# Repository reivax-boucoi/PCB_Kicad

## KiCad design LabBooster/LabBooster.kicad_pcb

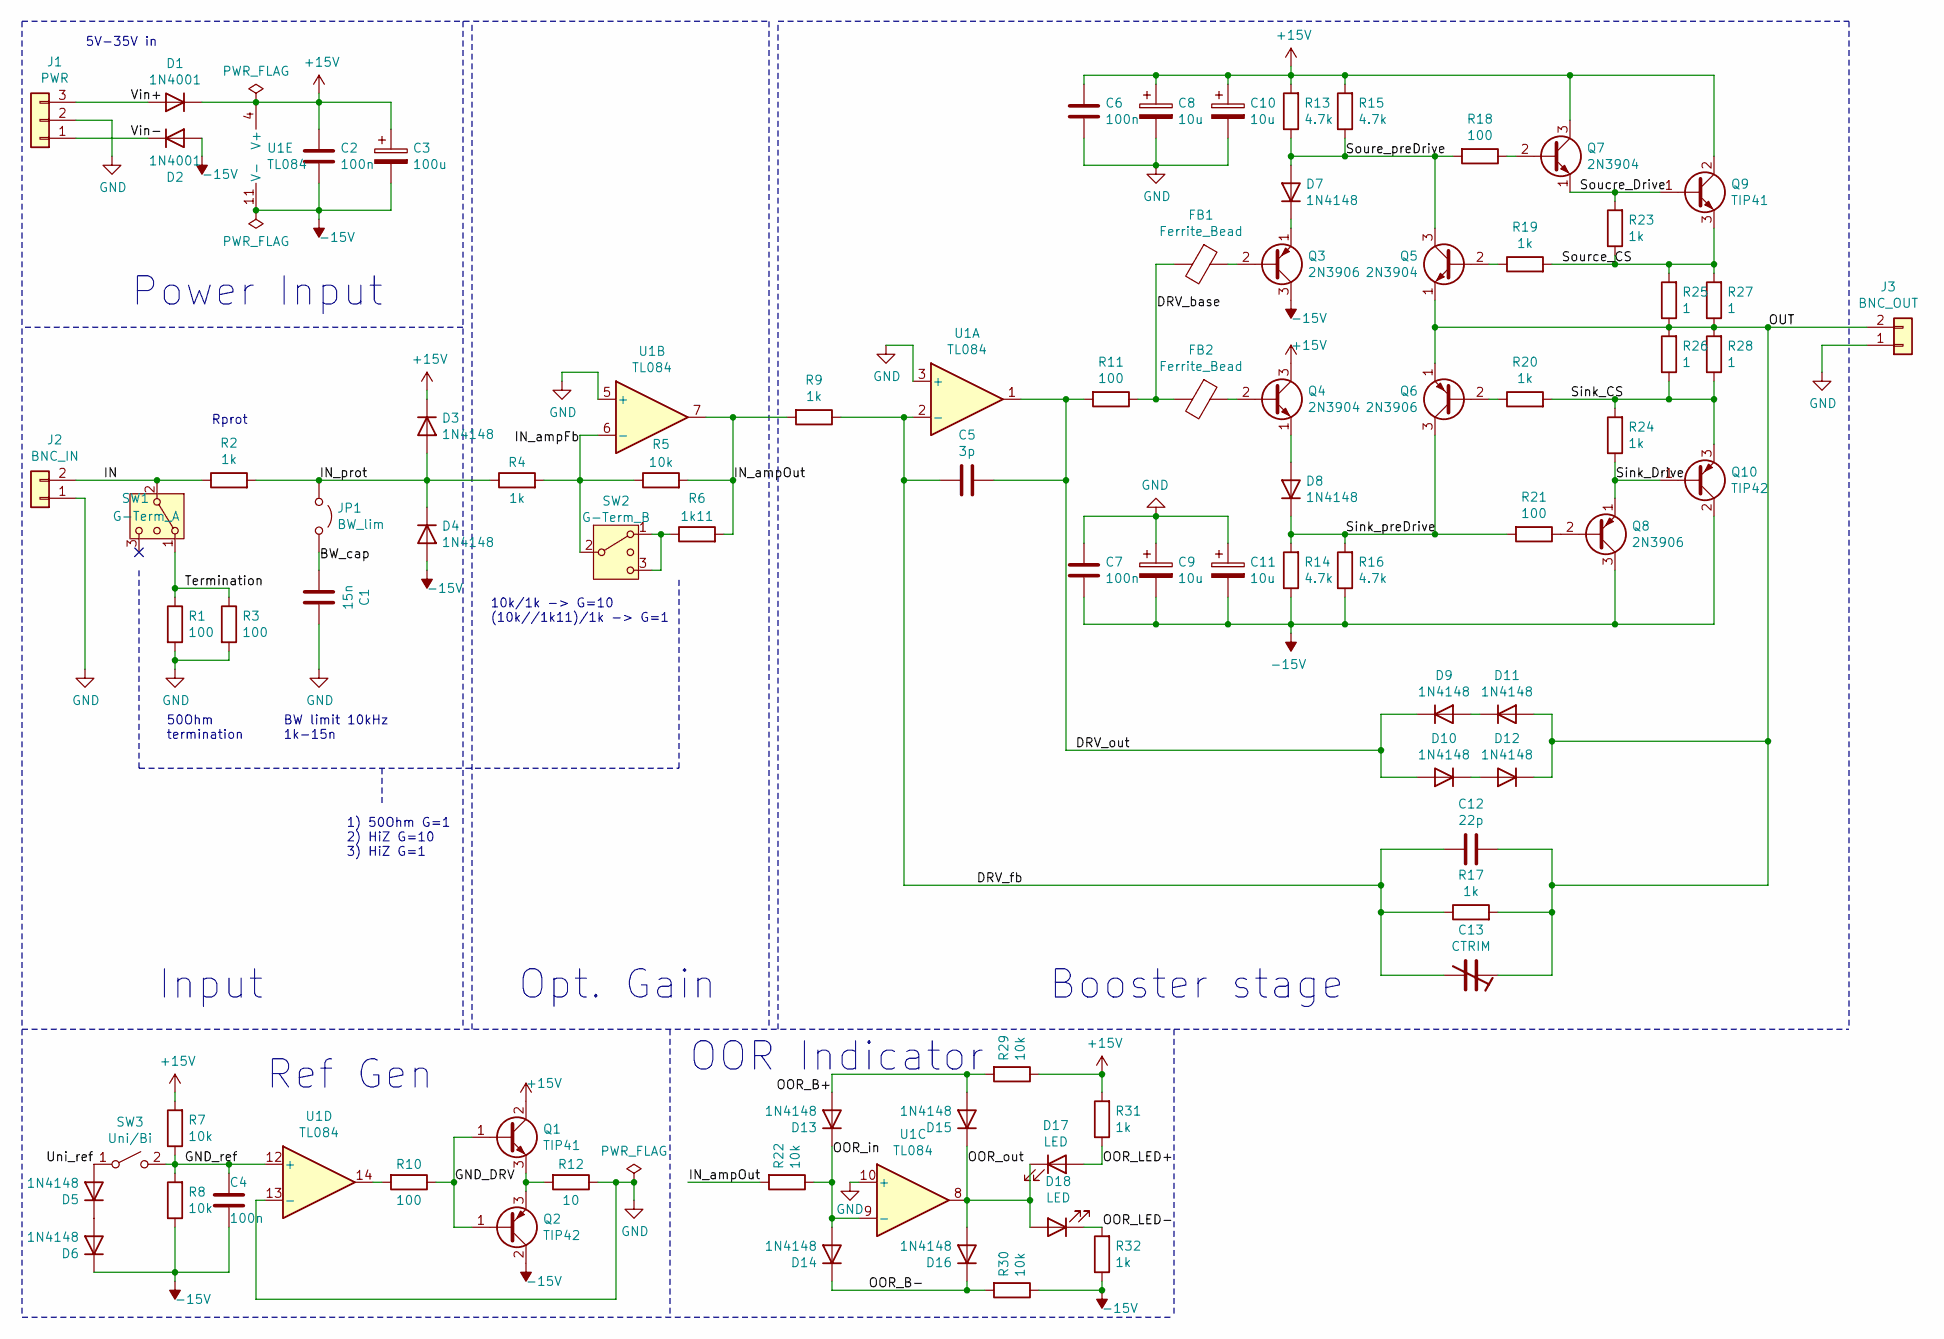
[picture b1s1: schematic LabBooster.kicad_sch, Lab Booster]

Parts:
C1: 15n; C_Socket_D5.0mm_W2.5mm_P5.00mm
C2, C4, C6, C7: 100n; C_Disc_D5.0mm_W2.5mm_P5.00mm
C3: 100u; CP_Radial_D10.0mm_P5.00mm
C5: 3p; C_Socket_D5.0mm_W2.5mm_P5.00mm
C8, C9, C10, C11: 10u; CP_Radial_D6.3mm_P2.50mm
C12: 22p; C_Socket_D5.0mm_W2.5mm_P5.00mm
C13: CTRIM
D1, D2: 1N4001; D_DO-41_SOD81_P10.16mm_Horizontal
D3, D4, D5, D6, D7, D8, D9, D10, D11, D12, D13, D14, D15, D16: 1N4148; D_DO-35_SOD27_P7.62mm_Horizontal
D17, D18: LED; LED_D3.0mm
FB1, FB2: Ferrite_Bead; R_Axial_DIN0309_L9.0mm_D3.2mm_P12.70mm_Horizontal
J1: PWR; SolderWirePad_1x03_P4.445mm_Drill1.5mm
J2: BNC_IN; SolderWirePad_1x02_P5.08mm_Drill1.5mm
J3: BNC_OUT; SolderWirePad_1x02_P5.08mm_Drill1.5mm
JP1: BW_lim; PinSocket_1x02_P2.54mm_Vertical
Q1, Q9: TIP41; TO-220-3_Vertical
Q2, Q10: TIP42; TO-220-3_Vertical
Q3, Q6, Q8: 2N3906; TO-92_Inline
Q4, Q5, Q7: 2N3904; TO-92_Inline
R1, R3, R10, R11, R18, R21: 100; R_Axial_DIN0207_L6.3mm_D2.5mm_P10.16mm_Horizontal
R2: 1k; R_Socket_L6.3mm_D2.5mm_P10.16mm_Horizontal
R4, R9, R17, R19, R20, R23, R24, R31, R32: 1k; R_Axial_DIN0207_L6.3mm_D2.5mm_P10.16mm_Horizontal
R5, R7, R8, R29, R30: 10k; R_Axial_DIN0207_L6.3mm_D2.5mm_P10.16mm_Horizontal
R6: 1k11; R_Socket_L6.3mm_D2.5mm_P10.16mm_Horizontal
R12: 10; R_Socket_L6.3mm_D2.5mm_P10.16mm_Horizontal
R13, R14, R15, R16: 4.7k; R_Axial_DIN0207_L6.3mm_D2.5mm_P10.16mm_Horizontal
R22: 10k; R_Socket_L6.3mm_D2.5mm_P10.16mm_Horizontal
R25, R26, R27, R28: 1; R_Axial_DIN0207_L6.3mm_D2.5mm_P10.16mm_Horizontal
SW1: G-Term_A; PinHeader_1x03_P2.54mm_Vertical
SW2: G-Term_B; PinHeader_1x03_P2.54mm_Vertical
SW3: Uni/Bi; PinSocket_1x02_P2.54mm_Vertical
U1: TL084; DIP-14_W7.62mm

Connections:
+15V: C2.1, C3.1, C6.1, C8.1, C10.1, D1.1 (K), D3.1 (K), Q1.2 (C), Q4.3 (C), Q7.3 (C), Q9.2 (C), R7.2, R13.2, R15.2, R29.1, R31.2, U1.4 (V+)
-15V: C2.2, C3.2, C4.2, C7.2, C9.2, C11.2, D2.2 (A), D4.2 (A), D6.1 (K), Q2.2 (C), Q3.3 (C), Q8.3 (C), Q10.2 (C), R8.1, R14.1, R16.1, R30.1, R32.1, U1.11 (V-)
/BW_cap: C1.2, JP1.2 (B)
/DRV_base: FB1.2, FB2.2, R11.1
/DRV_fb: C5.2, C12.2, C13.2, R9.1, R17.1, U1.2 (-)
/DRV_out: C5.1, D9.1 (K), D10.2 (A), R11.2, U1.1
/GND_DRV: Q1.1 (B), Q2.1 (B), R10.1
/GND_ref: C4.1, R7.1, R8.2, SW3.2 (B), U1.12 (+)
/IN: J2.2, R2.1, SW1.2 (3)
/IN_ampFb: R4.2, R5.1, SW2.2 (3), U1.6 (-)
/IN_ampOut: R5.2, R6.2, R9.2, R22.2, U1.7
/IN_prot: D3.2 (A), D4.1 (K), JP1.1 (A), R2.2, R4.1
/OOR_B+: D13.2 (A), D15.2 (A), R29.2
/OOR_B-: D14.1 (K), D16.1 (K), R30.2
/OOR_LED+: D17.2 (A), R31.1
/OOR_LED-: D18.1 (K), R32.2
/OOR_in: D13.1 (K), D14.2 (A), R22.1, U1.9 (-)
/OOR_out: D15.1 (K), D16.2 (A), D17.1 (K), D18.2 (A), U1.8
/OUT: C12.1, C13.1, D11.2 (A), D12.1 (K), J3.2, Q5.1 (E), Q6.1 (E), R17.2, R25.1, R26.2, R27.1, R28.2
/Sink_CS: Q10.3 (E), R20.2, R24.2, R26.1, R28.1
/Sink_Drive: Q8.1 (E), Q10.1 (B), R24.1
/Sink_preDrive: D8.1 (K), Q6.3 (C), R14.2, R16.2, R21.2
/Soucre_Drive: Q7.1 (E), Q9.1 (B), R23.2
/Source_CS: Q9.3 (E), R19.2, R23.1, R25.2, R27.2
/Soure_preDrive: D7.2 (A), Q5.3 (C), R13.1, R15.1, R18.2
/Termination: R1.1, R3.1, SW1.1
/Uni_ref: D5.2 (A), SW3.1 (A)
/Vin+: D1.2 (A), J1.3
/Vin-: D2.1 (K), J1.1
GND: C1.1, C6.2, C7.1, C8.2, C9.1, C10.2, C11.1, J1.2, J2.1, J3.1, R1.2, R3.2, R12.1, U1.3 (+), U1.5 (+), U1.10 (+), U1.13 (-)
unnamed: D5.1 (K), D6.2 (A)
unnamed: D7.1 (K), Q3.1 (E)
unnamed: D8.2 (A), Q4.1 (E)
unnamed: D10.1 (K), D12.2 (A)
unnamed: D9.2 (A), D11.1 (K)
unnamed: FB1.1, Q3.2 (B)
unnamed: FB2.1, Q4.2 (B)
unnamed: Q1.3 (E), Q2.3 (E), R12.2
unnamed: Q5.2 (B), R19.1
unnamed: Q6.2 (B), R20.1
unnamed: Q7.2 (B), R18.1
unnamed: Q8.2 (B), R21.1
unnamed: R6.1, SW2.1, SW2.3 (4)
unnamed: R10.2, U1.14

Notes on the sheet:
5V-35V in
Opt. Gain
Power Input
50Ohm termination
Input
10k/1k -> G=10 (10k//1k11)/1k -> G=1
Ref Gen
BW limit 10kHz 1k-15n
1) 50Ohm G=1 2) HiZ G=10 3) HiZ G=1
Booster stage
Rprot
OOR Indicator

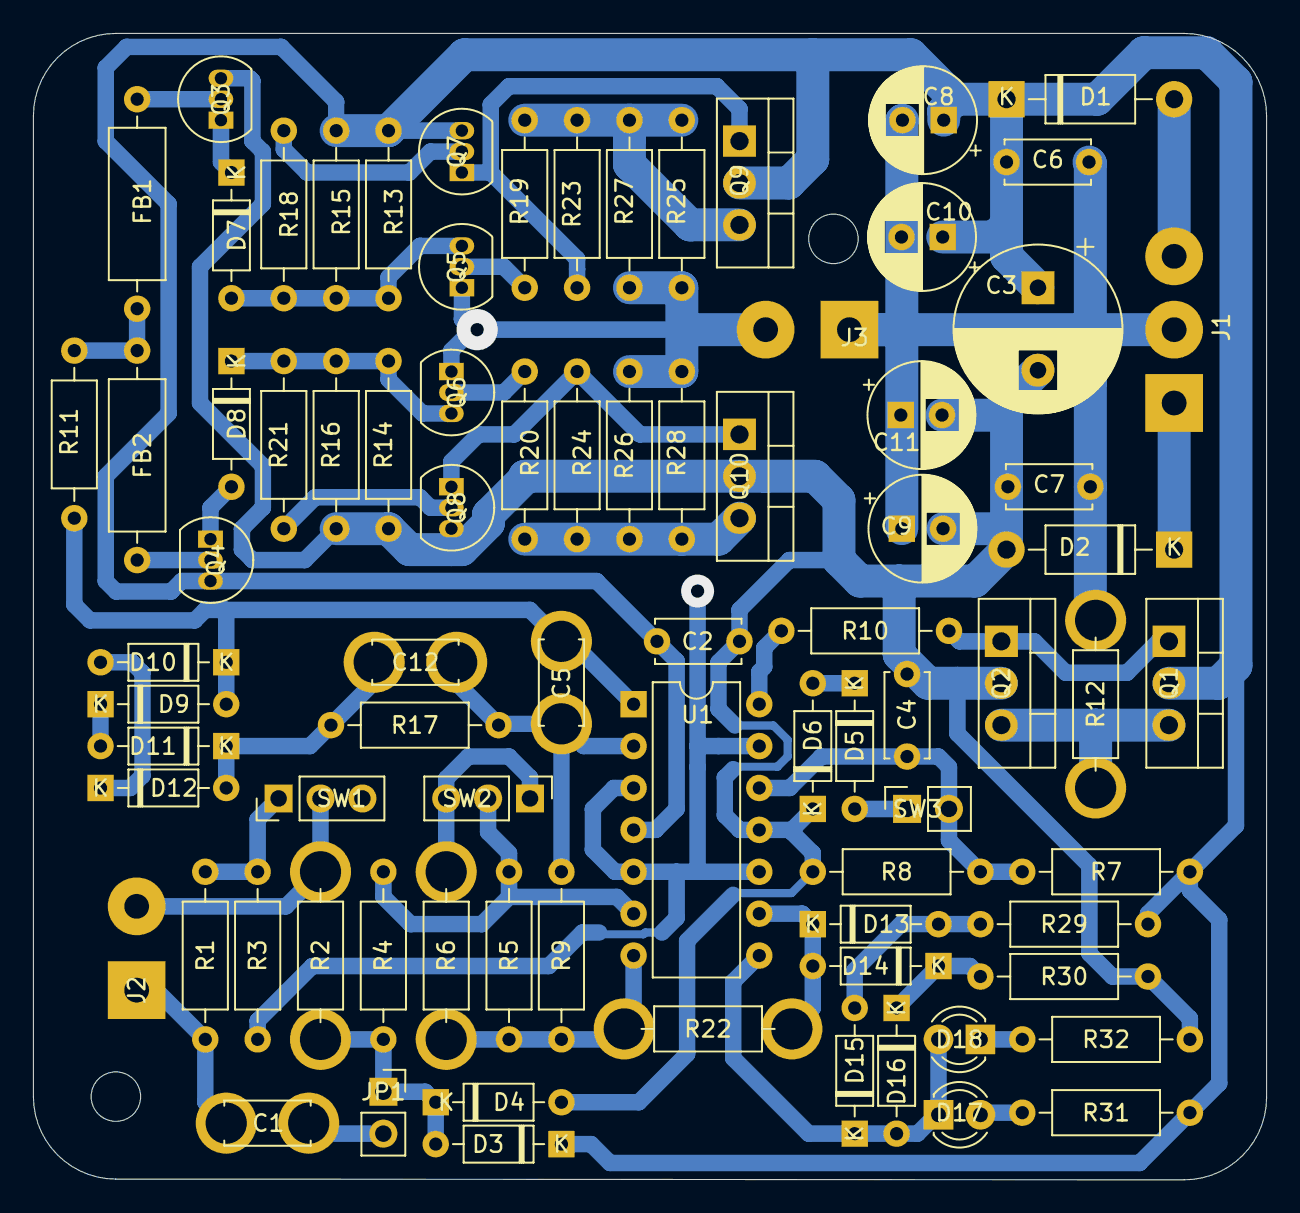
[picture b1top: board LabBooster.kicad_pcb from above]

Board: 2 copper layers, 74.8 x 69.5 mm, 82 parts (0 on the bottom side), 44 nets.

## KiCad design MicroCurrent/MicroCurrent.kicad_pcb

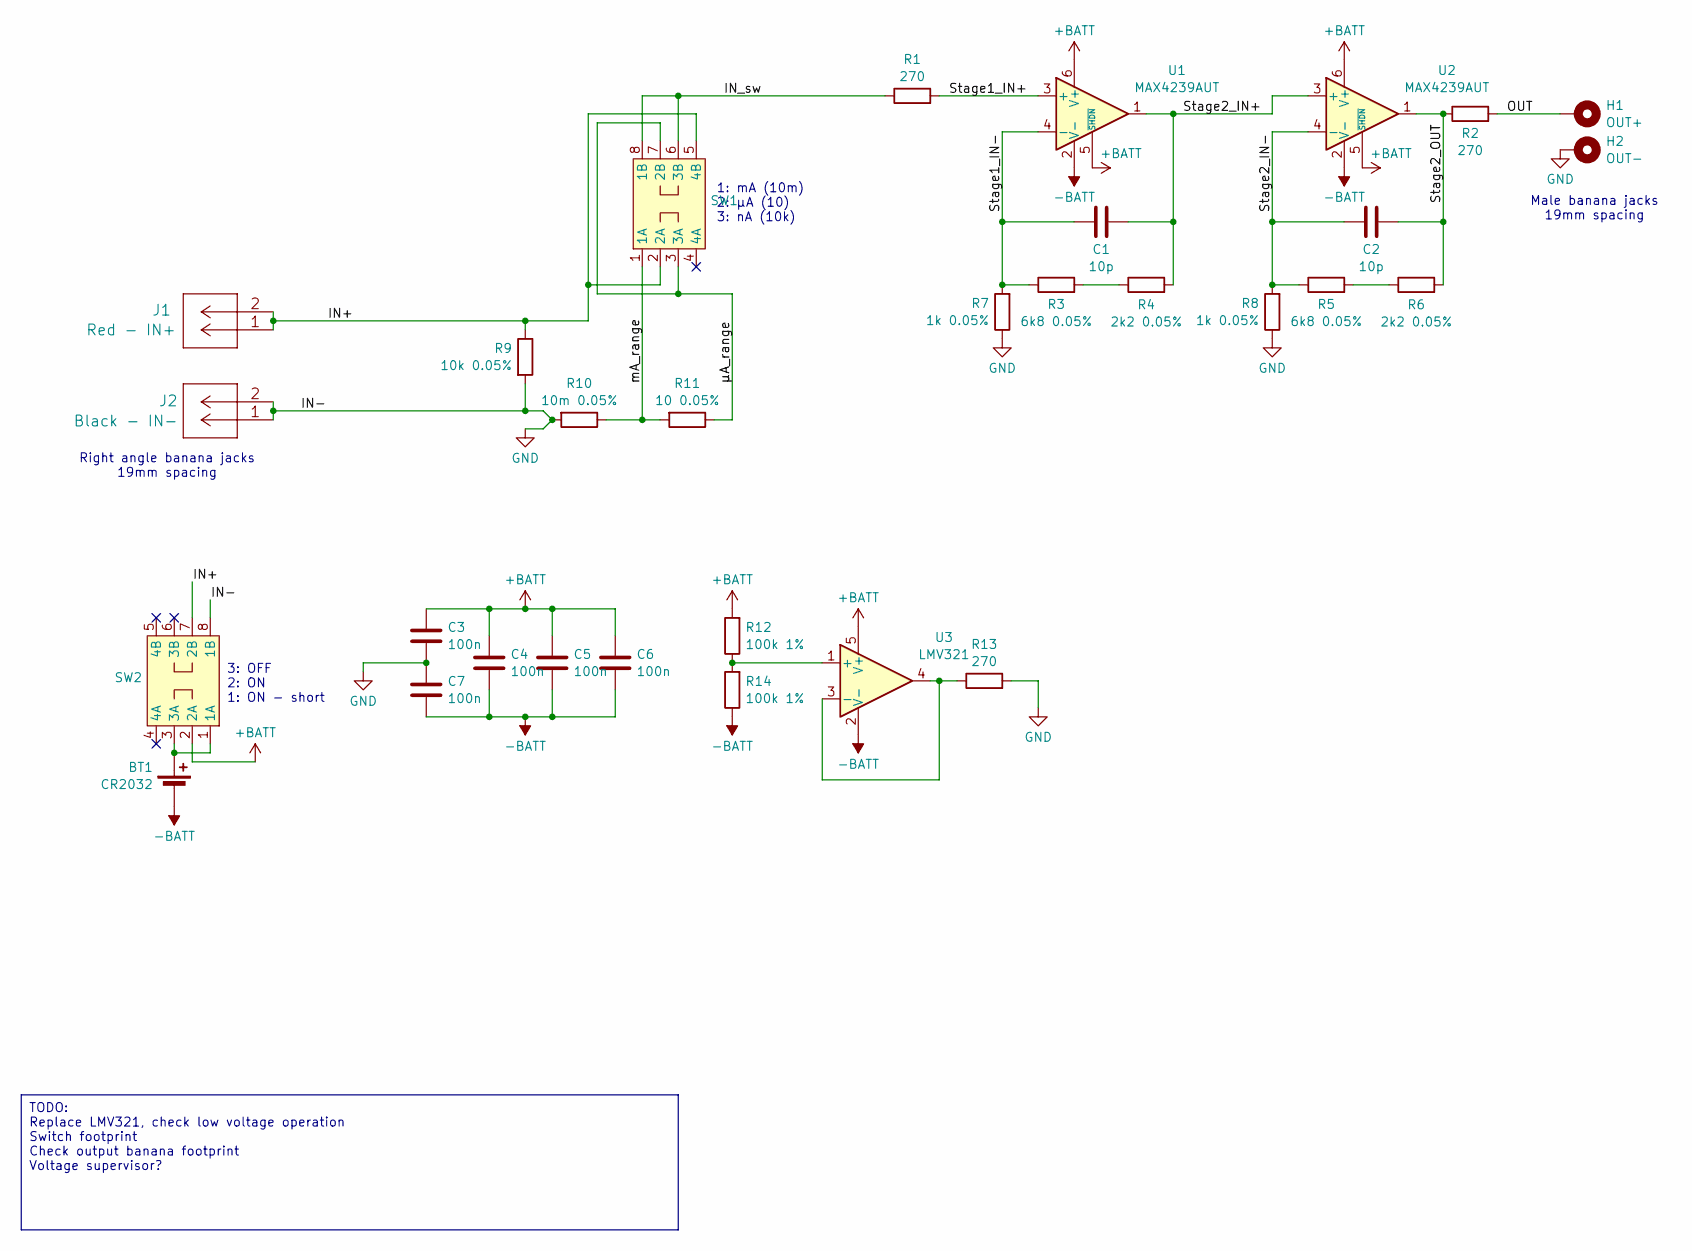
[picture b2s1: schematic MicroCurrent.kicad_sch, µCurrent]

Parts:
BT1: CR2032; BatteryHolder_Multicomp_BC-2001_1x2032
C1, C2: 10p; C_0603_1608Metric_Pad1.08x0.95mm_HandSolder
C3, C4, C5, C6, C7: 100n; C_0603_1608Metric_Pad1.08x0.95mm_HandSolder
H1: OUT+; MountingHole_4.3mm_M4_Pad_Via
H2: OUT-; MountingHole_4.3mm_M4_Pad_Via
J1: Red - IN+; 571-0100_Black
J2: Black - IN-; 571-0100_Black
R1, R2, R13: 270; R_0805_2012Metric_Pad1.20x1.40mm_HandSolder
R3, R5: 6k8 0.05%; R_0603_1608Metric_Pad0.98x0.95mm_HandSolder
R4, R6: 2k2 0.05%; R_0603_1608Metric_Pad0.98x0.95mm_HandSolder
R7, R8: 1k 0.05%; R_0603_1608Metric_Pad0.98x0.95mm_HandSolder
R9: 10k 0.05%; R_0603_1608Metric_Pad0.98x0.95mm_HandSolder
R10: 10m 0.05%; R_2512_6332Metric_Pad1.40x3.35mm_HandSolder
R11: 10 0.05%; R_0805_2012Metric_Pad1.20x1.40mm_HandSolder
R12, R14: 100k 1%; R_0603_1608Metric_Pad0.98x0.95mm_HandSolder
SW1, SW2: L203011MS02Q_3PDT_switch
U1, U2: MAX4239AUT; SOT-23-6
U3: LMV321; SOT-23-5_HandSoldering

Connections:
+BATT: C3.1, C4.1, C5.1, C6.1, R12.2, SW2.2 (2A), U1.5 (~SHDN), U1.6 (V+), U2.5 (~SHDN), U2.6 (V+), U3.5 (V+)
-BATT: BT1.2 (-), C4.2, C5.2, C6.2, C7.2, R14.1, U1.2 (V-), U2.2 (V-), U3.2 (V-)
/IN+: J1.1, J1.2, R9.1, SW1.2 (2A), SW1.5 (4B), SW2.7 (2B)
/IN_sw: R1.1, SW1.6 (3B), SW1.8 (1B)
/OUT: H1.1, R2.2
/Stage1_IN+: R1.2, U1.3 (+)
/Stage1_IN-: C1.1, R3.1, R7.2, U1.4 (-)
/Stage2_IN+: C1.2, R4.2, U1.1, U2.3 (+)
/Stage2_IN-: C2.1, R5.1, R8.2, U2.4 (-)
/Stage2_OUT: C2.2, R2.1, R6.2, U2.1
/mA_range: R10.1, R11.2, SW1.1 (1A)
/µA_range: R11.1, SW1.3 (3A), SW1.7 (2B)
GND: C3.2, C7.1, H2.1, J2.1, J2.2, R7.1, R8.1, R9.2, R10.2, R13.2, SW2.8 (1B)
unnamed: BT1.1 (+), SW2.1 (1A), SW2.3 (3A)
unnamed: R3.2, R4.1
unnamed: R5.2, R6.1
unnamed: R12.1, R14.2, U3.1 (+)
unnamed: R13.1, U3.3 (-), U3.4

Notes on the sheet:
TODO: Replace LMV321, check low voltage operation Switch footprint Check output banana footprint Voltage supervisor?
Right angle banana jacks 19mm spacing
3: OFF 2: ON 1: ON - short
1: mA (10m) 2: µA (10) 3: nA (10k)
Male banana jacks 19mm spacing

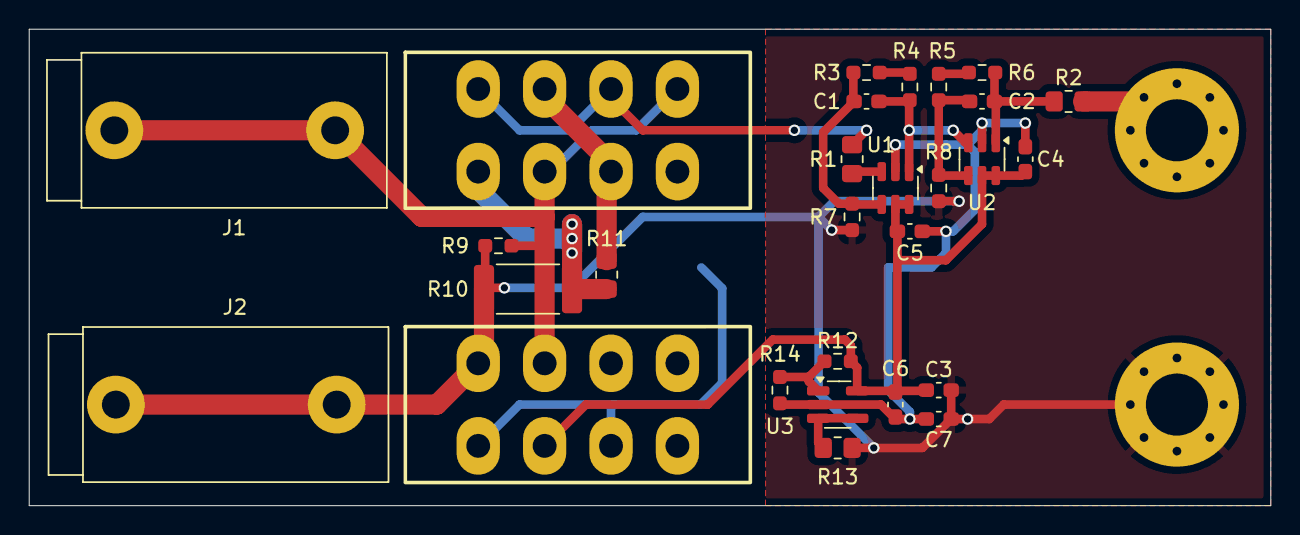
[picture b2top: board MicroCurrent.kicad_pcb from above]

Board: 2 copper layers, 86.0 x 33.0 mm, 31 parts (1 on the bottom side), 18 nets.

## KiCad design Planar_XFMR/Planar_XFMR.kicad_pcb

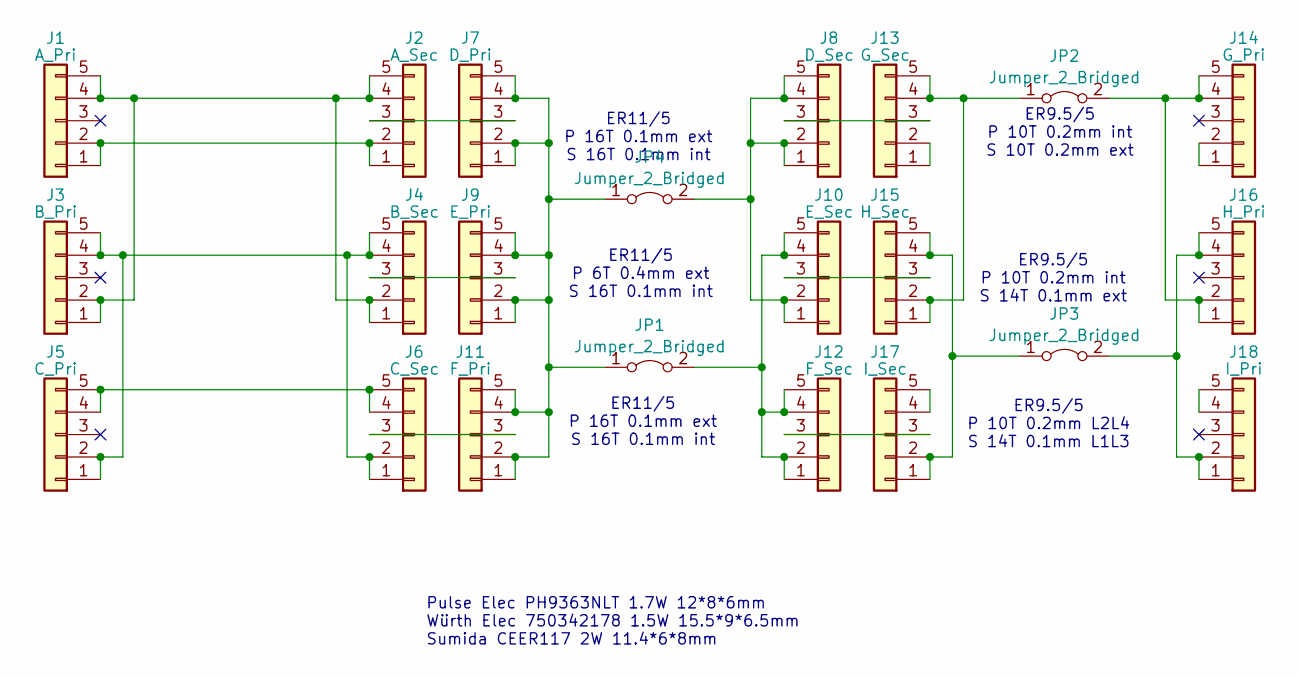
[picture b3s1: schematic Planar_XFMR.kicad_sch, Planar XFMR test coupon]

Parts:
J1: A_Pri; PinHeader_1x05_P2.54mm_Vertical
J2: A_Sec; PinHeader_1x05_P2.54mm_Vertical
J3: B_Pri; PinHeader_1x05_P2.54mm_Vertical
J4: B_Sec; PinHeader_1x05_P2.54mm_Vertical
J5: C_Pri; PinHeader_1x05_P2.54mm_Vertical
J6: C_Sec; PinHeader_1x05_P2.54mm_Vertical
J7: D_Pri; PinHeader_1x05_P2.54mm_Vertical
J8: D_Sec; PinHeader_1x05_P2.54mm_Vertical
J9: E_Pri; PinHeader_1x05_P2.54mm_Vertical
J10: E_Sec; PinHeader_1x05_P2.54mm_Vertical
J11: F_Pri; PinHeader_1x05_P2.54mm_Vertical
J12: F_Sec; PinHeader_1x05_P2.54mm_Vertical
J13: G_Sec; PinHeader_1x05_P2.54mm_Vertical
J14: G_Pri; PinHeader_1x05_P2.54mm_Vertical
J15: H_Sec; PinHeader_1x05_P2.54mm_Vertical
J16: H_Pri; PinHeader_1x05_P2.54mm_Vertical
J17: I_Sec; PinHeader_1x05_P2.54mm_Vertical
J18: I_Pri; PinHeader_1x05_P2.54mm_Vertical
JP1, JP2, JP3, JP4: Jumper_2_Bridged; SolderJumper-2_P1.3mm_Bridged_RoundedPad1.0x1.5mm

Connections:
unnamed: J1.1, J1.2, J2.1, J2.2
unnamed: J1.4, J1.5, J2.4, J2.5, J3.1, J3.2, J4.1, J4.2
unnamed: J2.3, J7.3
unnamed: J3.4, J3.5, J4.4, J4.5, J5.1, J5.2, J6.1, J6.2
unnamed: J4.3, J9.3
unnamed: J5.4, J5.5, J6.4, J6.5
unnamed: J8.1, J8.2, J8.4, J8.5, J10.1, J10.2, JP4.2 (B)
unnamed: J10.3, J15.3
unnamed: J10.4, J10.5, J12.1, J12.2, J12.4, J12.5, JP1.2 (B)
unnamed: J7.1, J7.2, J7.4, J7.5, J9.1, J9.2, J9.4, J9.5, J11.1, J11.2, J11.4, J11.5, JP1.1 (A), JP4.1 (A)
unnamed: J6.3, J11.3
unnamed: J12.3, J17.3
unnamed: J13.1, J13.2
unnamed: J8.3, J13.3
unnamed: J13.4, J13.5, J15.1, J15.2, JP2.1 (A)
unnamed: J14.1, J14.2
unnamed: J14.4, J14.5, J16.1, J16.2, JP2.2 (B)
unnamed: J15.4, J15.5, J17.1, J17.2, JP3.1 (A)
unnamed: J16.4, J16.5, J18.1, J18.2, JP3.2 (B)
unnamed: J17.4, J17.5
unnamed: J18.4, J18.5

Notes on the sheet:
ER9.5/5 P 10T 0.2mm L2L4 S 14T 0.1mm L1L3
ER11/5 P 6T 0.4mm ext S 16T 0.1mm int
ER9.5/5 P 10T 0.2mm int S 14T 0.1mm ext
Pulse Elec PH9363NLT 1.7W 12*8*6mm Würth Elec 750342178 1.5W 15.5*9*6.5mm Sumida CEER117 2W 11.4*6*8mm
ER9.5/5 P 10T 0.2mm int S 10T 0.2mm ext
ER11/5 P 16T 0.1mm ext S 16T 0.1mm int

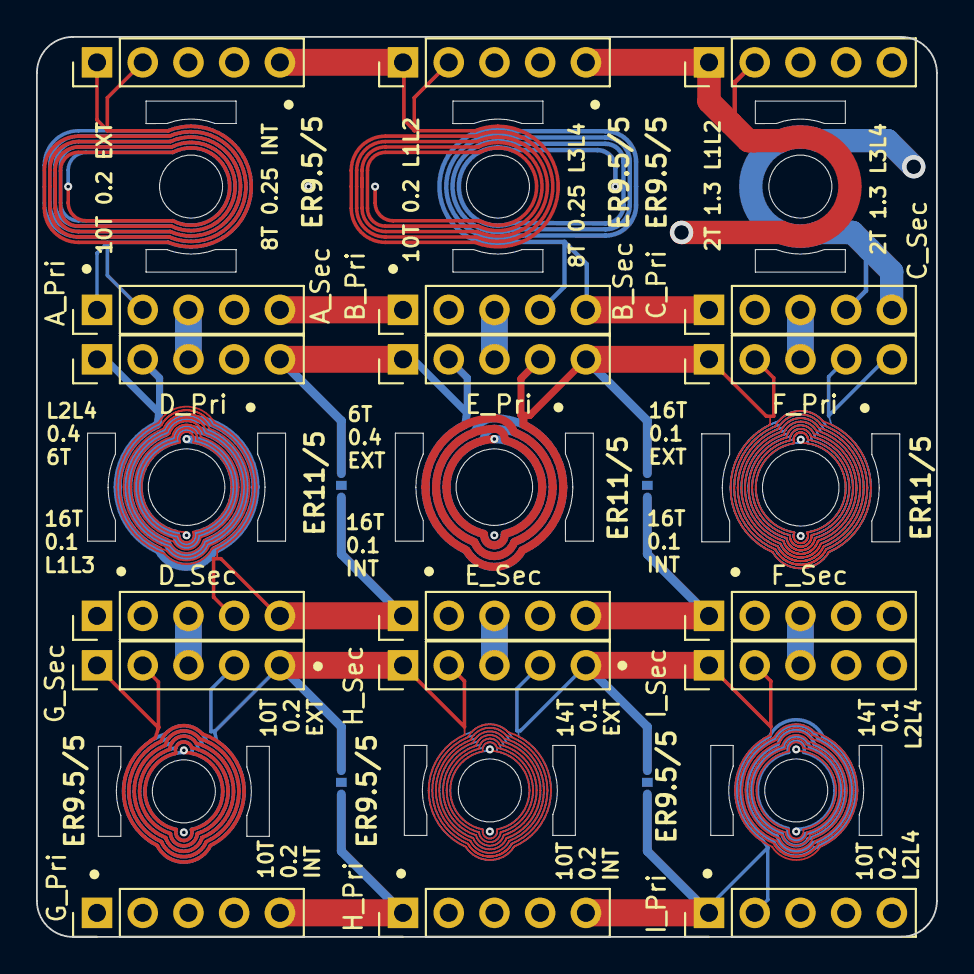
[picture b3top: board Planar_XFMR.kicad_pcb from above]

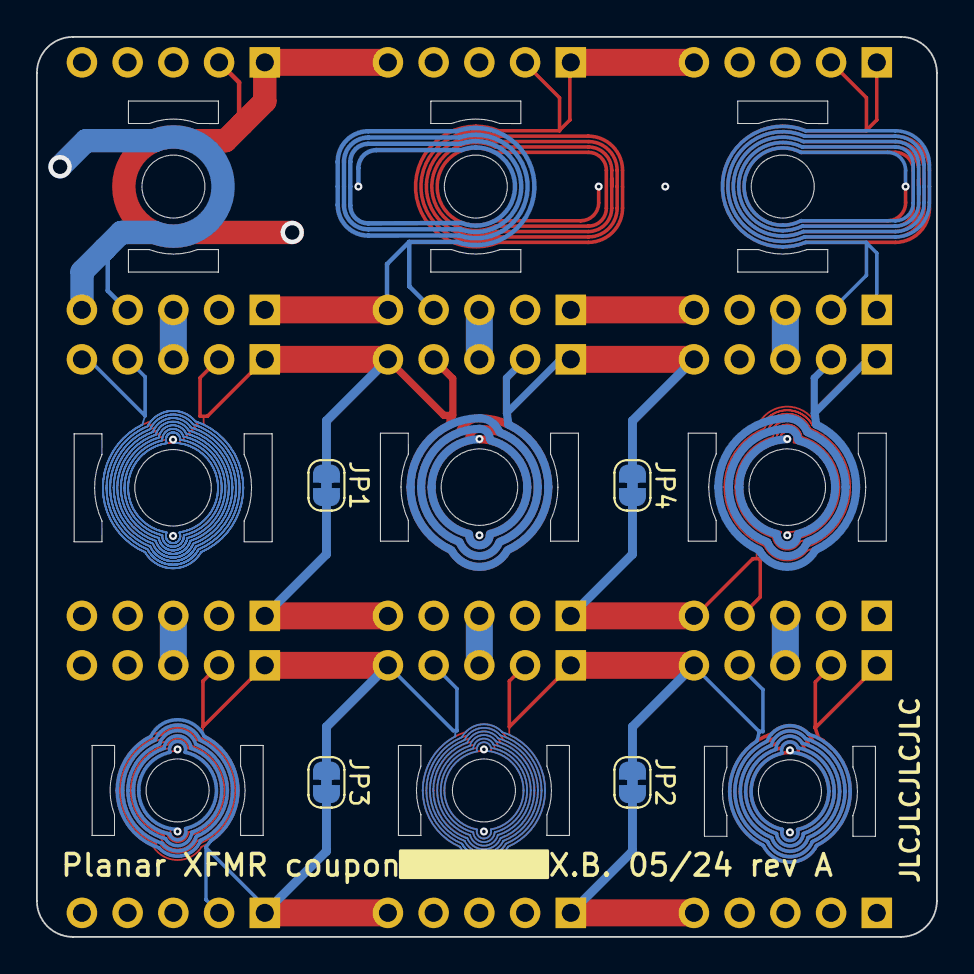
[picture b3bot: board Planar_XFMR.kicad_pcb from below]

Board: 4 copper layers, 50.0 x 50.0 mm, 22 parts (4 on the bottom side), 21 nets.

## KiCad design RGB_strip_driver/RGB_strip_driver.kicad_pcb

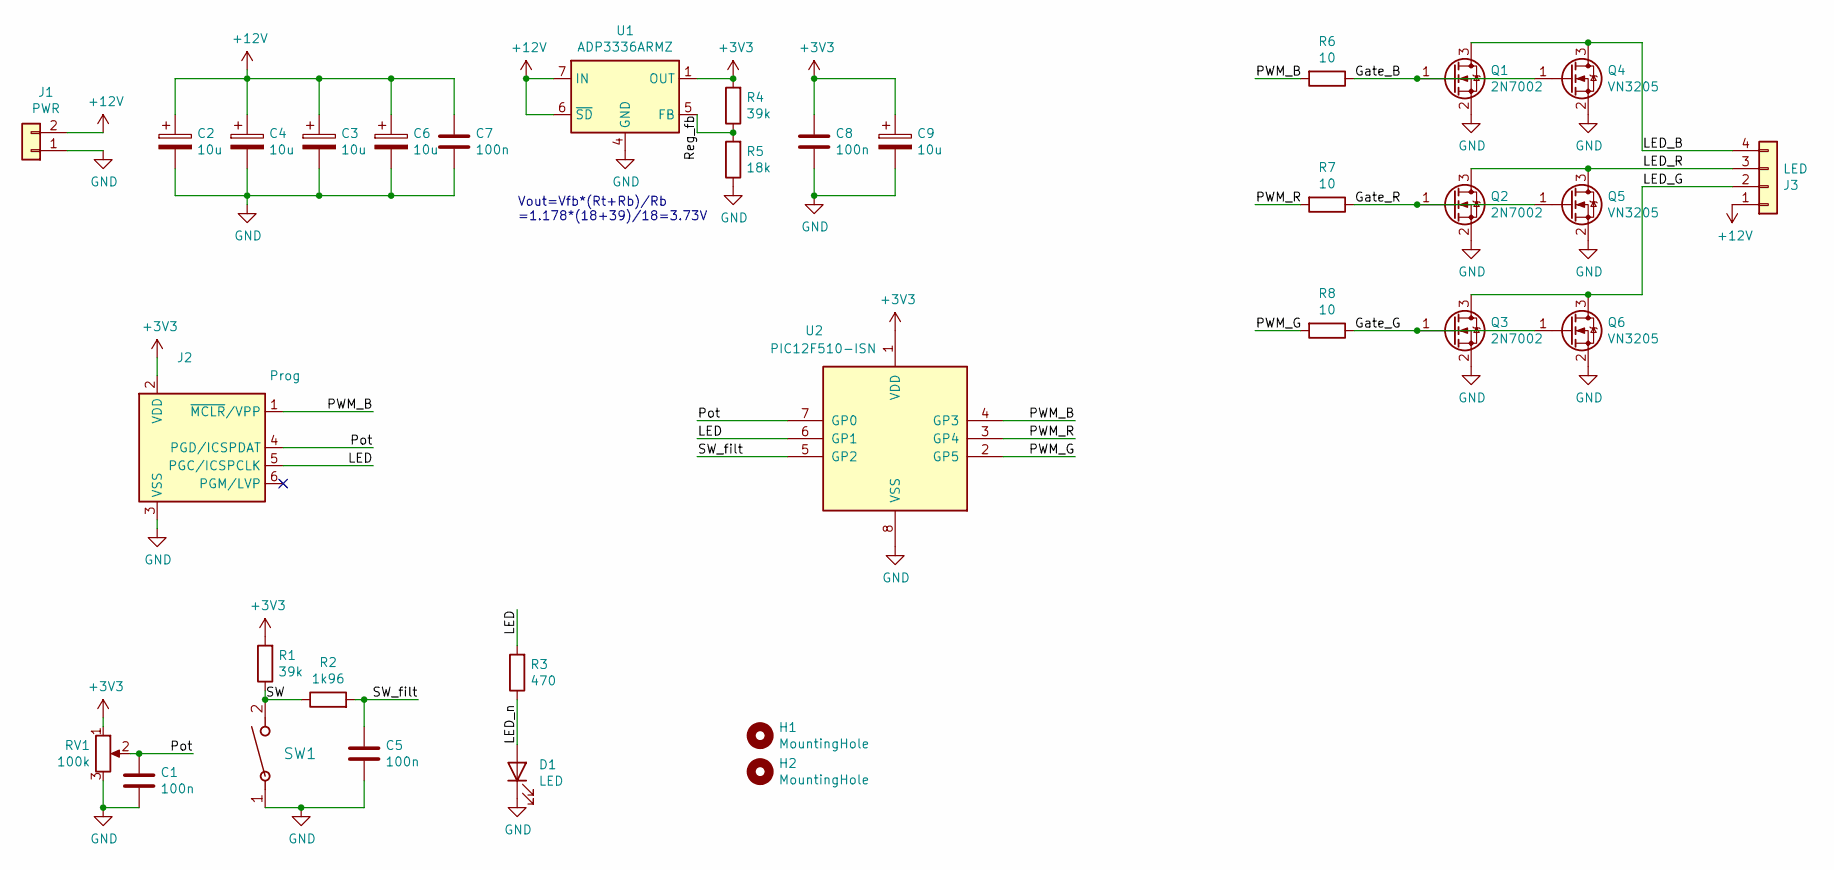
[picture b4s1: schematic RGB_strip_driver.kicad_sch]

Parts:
C1, C5, C7, C8: 100n; C_0603_1608Metric_Pad1.05x0.95mm_HandSolder
C2, C3, C4, C6, C9: 10u; C_1206_3216Metric_Pad1.42x1.75mm_HandSolder
D1: LED; LED_0805_2012Metric_Pad1.15x1.40mm_HandSolder
H1, H2: MountingHole; MountingHole_3.2mm_M3
J1: PWR; PinHeader_1x02_P2.54mm_Vertical
J2: Prog; Tag-Connect_TC2030-IDC-NL_2x03_P1.27mm_Vertical
J3: LED; PinHeader_1x04_P2.54mm_Vertical
Q1, Q2, Q3: 2N7002; SOT-23_Handsoldering
Q4, Q5, Q6: VN3205; SOT-89-3_Handsoldering
R1, R4: 39k; R_0603_1608Metric_Pad1.05x0.95mm_HandSolder
R2: 1k96; R_0603_1608Metric_Pad1.05x0.95mm_HandSolder
R3: 470; R_0603_1608Metric_Pad1.05x0.95mm_HandSolder
R5: 18k; R_0603_1608Metric_Pad1.05x0.95mm_HandSolder
R6, R7, R8: 10; R_0603_1608Metric_Pad1.05x0.95mm_HandSolder
RV1: 100k; Potentiometer_Piher_PT-10-H01_Horizontal
SW1: TL3330AF130QG; TL3330
U1: ADP3336ARMZ; MSOP-8_3x3mm_P0.65mm
U2: PIC12F510-ISN; SOIC-8_3.9x4.9mm_P1.27mm

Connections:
+3V3: C8.1, C9.1, J2.2 (VDD), R1.2, R4.2, RV1.1, U1.1 (OUT), U1.2 (OUT), U1.3 (OUT), U2.1 (VDD)
+12V: C2.1, C3.1, C4.1, C6.1, C7.1, J1.2, J3.1, U1.6 (~SD), U1.7 (IN), U1.8 (IN)
/Gate_B: Q1.1 (G), Q4.1 (G), R6.1
/Gate_G: Q3.1 (G), Q6.1 (G), R8.1
/Gate_R: Q2.1 (G), Q5.1 (G), R7.1
/LED: J2.5 (PGC/ICSPCLK), R3.2, U2.6 (GP1)
/LED_B: J3.4, Q1.3 (D), Q4.3 (D)
/LED_G: J3.2, Q3.3 (D), Q6.3 (D)
/LED_R: J3.3, Q2.3 (D), Q5.3 (D)
/LED_n: D1.2 (A), R3.1
/PWM_B: J2.1 (~MCLR/VPP), R6.2, U2.4 (GP3)
/PWM_G: R8.2, U2.2 (GP5)
/PWM_R: R7.2, U2.3 (GP4)
/Pot: C1.1, J2.4 (PGD/ICSPDAT), RV1.2, U2.7 (GP0)
/Reg_fb: R4.1, R5.2, U1.5 (FB)
/SW: R1.1, R2.1, SW1.2
/SW_filt: C5.1, R2.2, U2.5 (GP2)
GND: C1.2, C2.2, C3.2, C4.2, C5.2, C6.2, C7.2, C8.2, C9.2, D1.1 (K), J1.1, J2.3 (VSS), Q1.2 (S), Q2.2 (S), Q3.2 (S), Q4.2 (S), Q5.2 (S), Q6.2 (S), R5.1, RV1.3, SW1.1, U1.4 (GND), U2.8 (VSS)

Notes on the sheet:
Vout=Vfb*(Rt+Rb)/Rb =1.178*(18+39)/18=3.73V

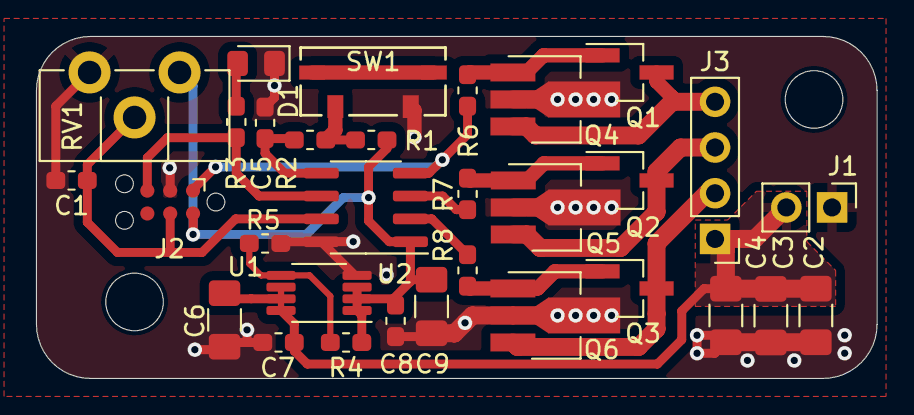
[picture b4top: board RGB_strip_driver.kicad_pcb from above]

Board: 2 copper layers, 46.7 x 19.0 mm, 33 parts (0 on the bottom side), 18 nets.

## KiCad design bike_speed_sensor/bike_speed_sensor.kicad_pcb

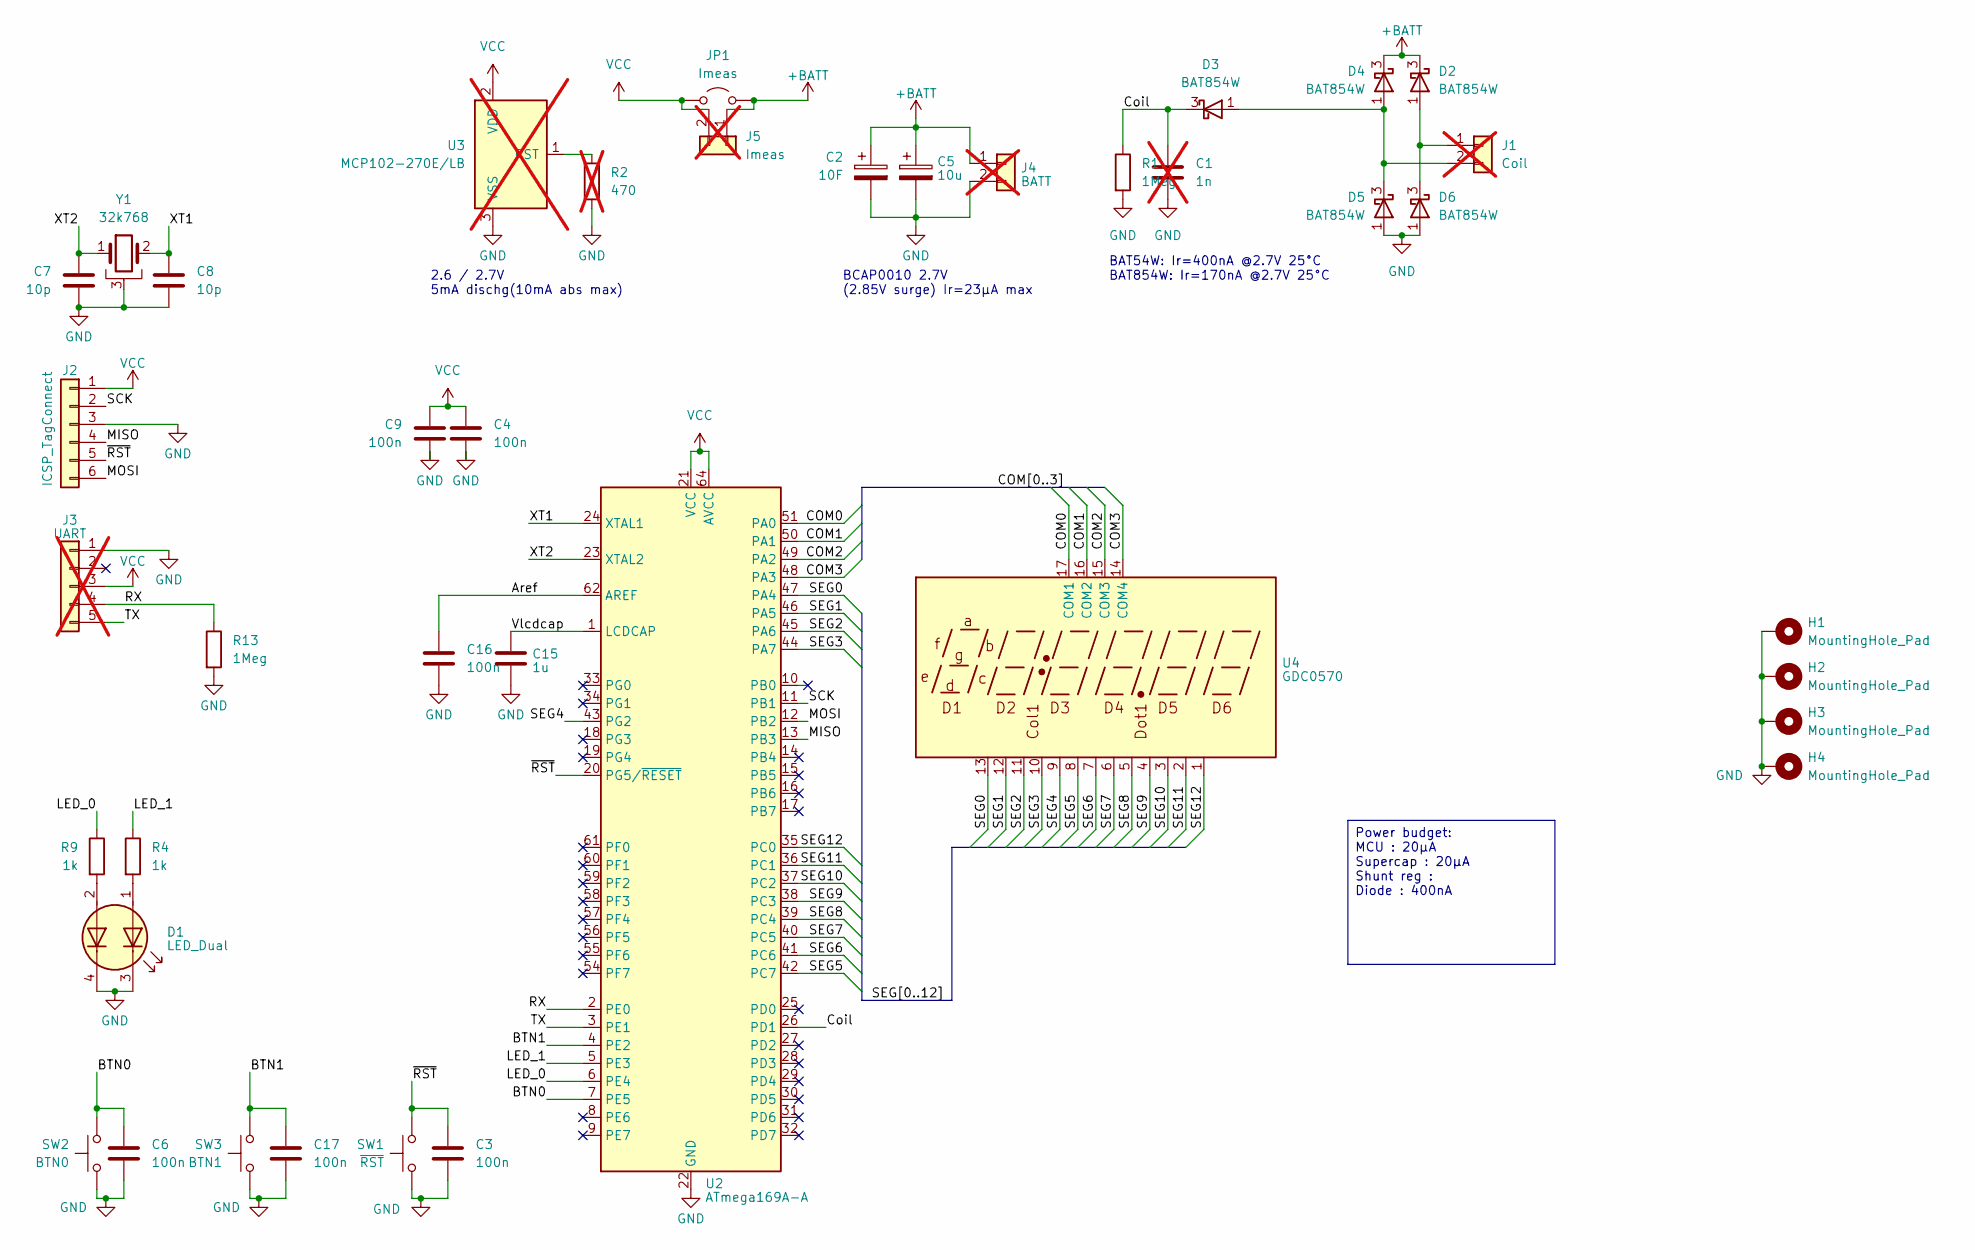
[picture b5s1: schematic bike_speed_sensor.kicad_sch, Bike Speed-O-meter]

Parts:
C1: 1n; C_0603_1608Metric; not fitted
C2: 10F; Board_edge_cap_P5mm_D10mm
C3, C4, C6, C9, C16, C17: 100n; C_0603_1608Metric
C5: 10u; C_1206_3216Metric_Pad1.33x1.80mm_HandSolder
C7, C8: 10p; C_0603_1608Metric
C15: 1u; C_0805_2012Metric_Pad1.18x1.45mm_HandSolder
D1: LED_Dual; LED_Cree-PLCC4_3.2x2.8mm_CCW
D2, D3, D4, D5, D6: BAT854W; SOT-323_SC-70_Handsoldering
H1, H2, H3, H4: MountingHole_Pad; MountingHole_3.2mm_M3_Pad_Via
J1: Coil; PinHeader_1x02_P2.54mm_Vertical; not fitted
J2: ICSP_TagConnect; Tag-Connect_TC2030-IDC-NL_2x03_P1.27mm_Vertical
J3: UART; PinSocket_1x05_P2.54mm_Vertical; not fitted
J4: BATT; PinHeader_1x02_P2.54mm_Vertical; not fitted
J5: Imeas; PinHeader_1x02_P2.54mm_Vertical; not fitted
JP1: Imeas; SolderJumper-2_P1.3mm_Open_RoundedPad1.0x1.5mm
R1, R13: 1Meg; R_0603_1608Metric
R2: 470; R_0603_1608Metric; not fitted
R4, R9: 1k; R_0603_1608Metric
SW1: ~{RST}; SW_PUSH_6mm_2pins
SW2: BTN0; SW_PUSH_6mm_2pins
SW3: BTN1; SW_PUSH_6mm_2pins
U2: ATmega169A-A; TQFP-64_14x14mm_P0.8mm
U3: MCP102-270E/LB; SOT-323_SC-70_Handsoldering; not fitted
U4: GDC0570; GDC0570_LCD_6digits_2mmPitch
Y1: 32k768; Crystal_SMD_MicroCrystal_MS1V-T1K

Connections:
+BATT: C2.1, C5.1, D2.3 (K), D4.3 (K), J4.1, J5.1, JP1.2 (B)
/Aref: C16.1, U2.62 (AREF)
/BTN0: C6.1, SW2.2, U2.7 (PE5)
/BTN1: C17.1, SW3.2, U2.4 (PE2)
/COM0: U2.51 (PA0), U4.17 (COM1)
/COM1: U2.50 (PA1), U4.16 (COM2)
/COM2: U2.49 (PA2), U4.15 (COM3)
/COM3: U2.48 (PA3), U4.14 (COM4)
/Coil: C1.1, D3.3 (K), R1.1, U2.26 (PD1)
/LED_0: R9.1, U2.6 (PE4)
/LED_1: R4.1, U2.5 (PE3)
/MISO: J2.4, U2.13 (PB3)
/MOSI: J2.6, U2.12 (PB2)
/RX: J3.4, R13.1, U2.2 (PE0)
/SCK: J2.2, U2.11 (PB1)
/SEG0: U2.47 (PA4), U4.13
/SEG1: U2.46 (PA5), U4.12
/SEG2: U2.45 (PA6), U4.11
/SEG3: U2.44 (PA7), U4.10
/SEG4: U2.43 (PG2), U4.9
/SEG5: U2.42 (PC7), U4.8
/SEG6: U2.41 (PC6), U4.7
/SEG7: U2.40 (PC5), U4.6
/SEG8: U2.39 (PC4), U4.5
/SEG9: U2.38 (PC3), U4.4
/SEG10: U2.37 (PC2), U4.3
/SEG11: U2.36 (PC1), U4.2
/SEG12: U2.35 (PC0), U4.1
/TX: J3.5, U2.3 (PE1)
/Vlcdcap: C15.1, U2.1 (LCDCAP)
/XT1: C8.1, U2.24 (XTAL1), Y1.2
/XT2: C7.1, U2.23 (XTAL2), Y1.1
/~RST: C3.1, J2.5, SW1.2, U2.20 (PG5/~RESET)
GND: C1.2, C2.2, C3.2, C4.2, C5.2, C6.2, C7.2, C8.2, C9.2, C15.2, C16.2, C17.2, D1.3 (K1), D1.4 (K2), D5.1 (A), D6.1 (A), H1.1, H2.1, H3.1, H4.1, J2.3, J3.1, J4.2, R1.2, R2.2, R13.2, SW1.1, SW2.1, SW3.1, U2.22 (GND), U2.53 (GND), U2.63 (GND), U3.3 (VSS), Y1.3
unnamed: D1.1 (A1), R4.2
unnamed: D1.2 (A2), R9.2
unnamed: D2.1 (A), D6.3 (K), J1.1
unnamed: D3.1 (A), D4.1 (A), D5.3 (K), J1.2
unnamed: R2.1, U3.1 (RST)
VCC: C4.1, C9.1, J2.1, J3.3, J5.2, JP1.1 (A), U2.21 (VCC), U2.52 (VCC), U2.64 (AVCC), U3.2 (VDD)

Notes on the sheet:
2.6 / 2.7V 5mA dischg(10mA abs max)
BCAP0010 2.7V (2.85V surge) Ir=23µA max
BAT54W: Ir=400nA @2.7V 25°C BAT854W: Ir=170nA @2.7V 25°C
Power budget: MCU : 20µA Supercap : 20µA Shunt reg : Diode : 400nA
